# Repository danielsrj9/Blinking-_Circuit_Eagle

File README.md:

# Blinking-_Circuit_Eagle
#Simple LED circuit board based on Jeremy Blum's Design

//This design used EAGLE 8.3.2 and is linked with FUSION 360

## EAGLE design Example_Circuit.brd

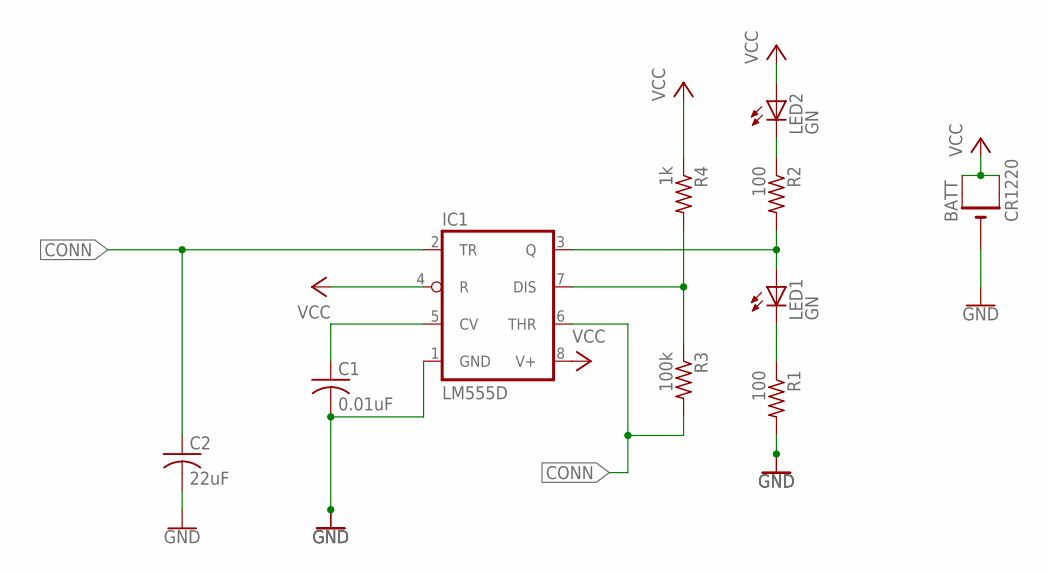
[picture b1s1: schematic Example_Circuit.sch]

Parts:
BATT: CR1220; CR1220-SMD
C1: 0.01uF; C0805; MPN VJ0805A103JXJTW1BC
C2: 22uF; C0805; MPN C0805C226M8PACTU
IC1: LM555D; SO08; MPN LMC555CM/NOPB
LED1, LED2: GN; CHIPLED_0805; MPN MCL-S270GC
R1, R2: 100; R0805; MPN ERJ-3EKF1270V
R3: 100k; R0805; MPN CPF0805B100KE1
R4: 1k; R0805; MPN CRCW04021K00FKTD

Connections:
CONN: C2.1, IC1.2 (TR), IC1.6 (THR), R3.2
GND: BATT.-, C1.2, C2.2, IC1.1 (GND), R1.2
unnamed: LED2.C, R2.1
unnamed: IC1.3 (Q), LED1.A, R2.2
unnamed: LED1.C, R1.1
unnamed: C1.1, IC1.5 (CV)
unnamed: IC1.7 (DIS), R3.1, R4.2
VCC: BATT.+$1 (+), BATT.+$2 (+1), IC1.4 (R), IC1.8 (V+), LED2.A, R4.1

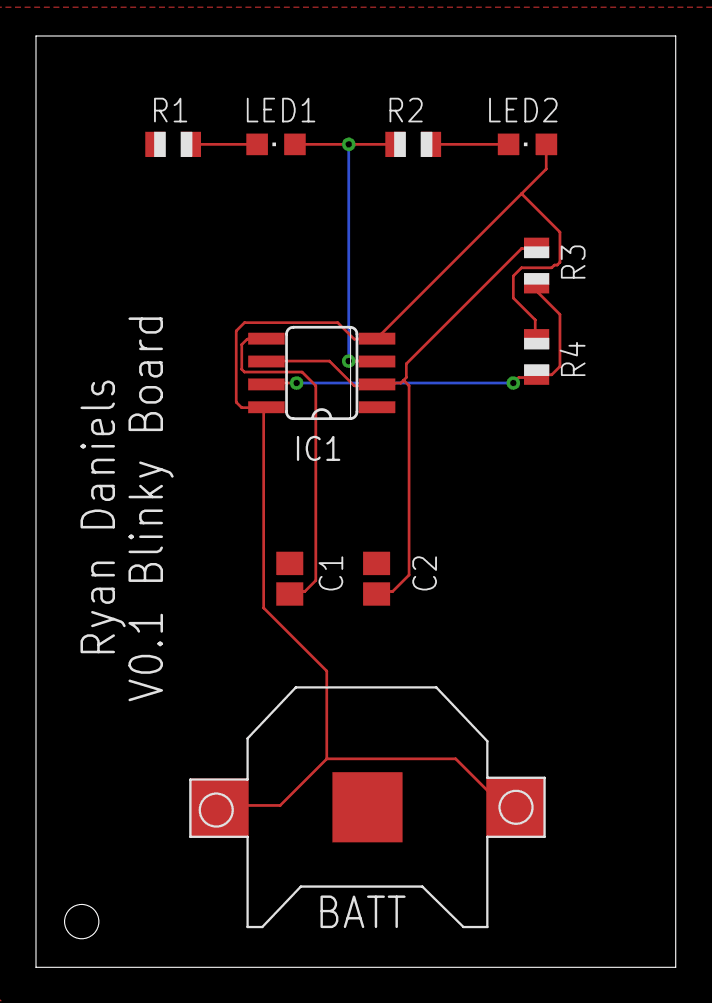
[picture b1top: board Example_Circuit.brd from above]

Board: 2 copper layers, 35.5 x 51.7 mm, 10 parts (0 on the bottom side), 8 nets.

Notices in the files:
parts and their libraries:
SparkFun-PowerSymbols: Licensing: Creative Commons ShareAlike 4.0 International - https://creativecommons.org/licenses/by-sa/4.0
